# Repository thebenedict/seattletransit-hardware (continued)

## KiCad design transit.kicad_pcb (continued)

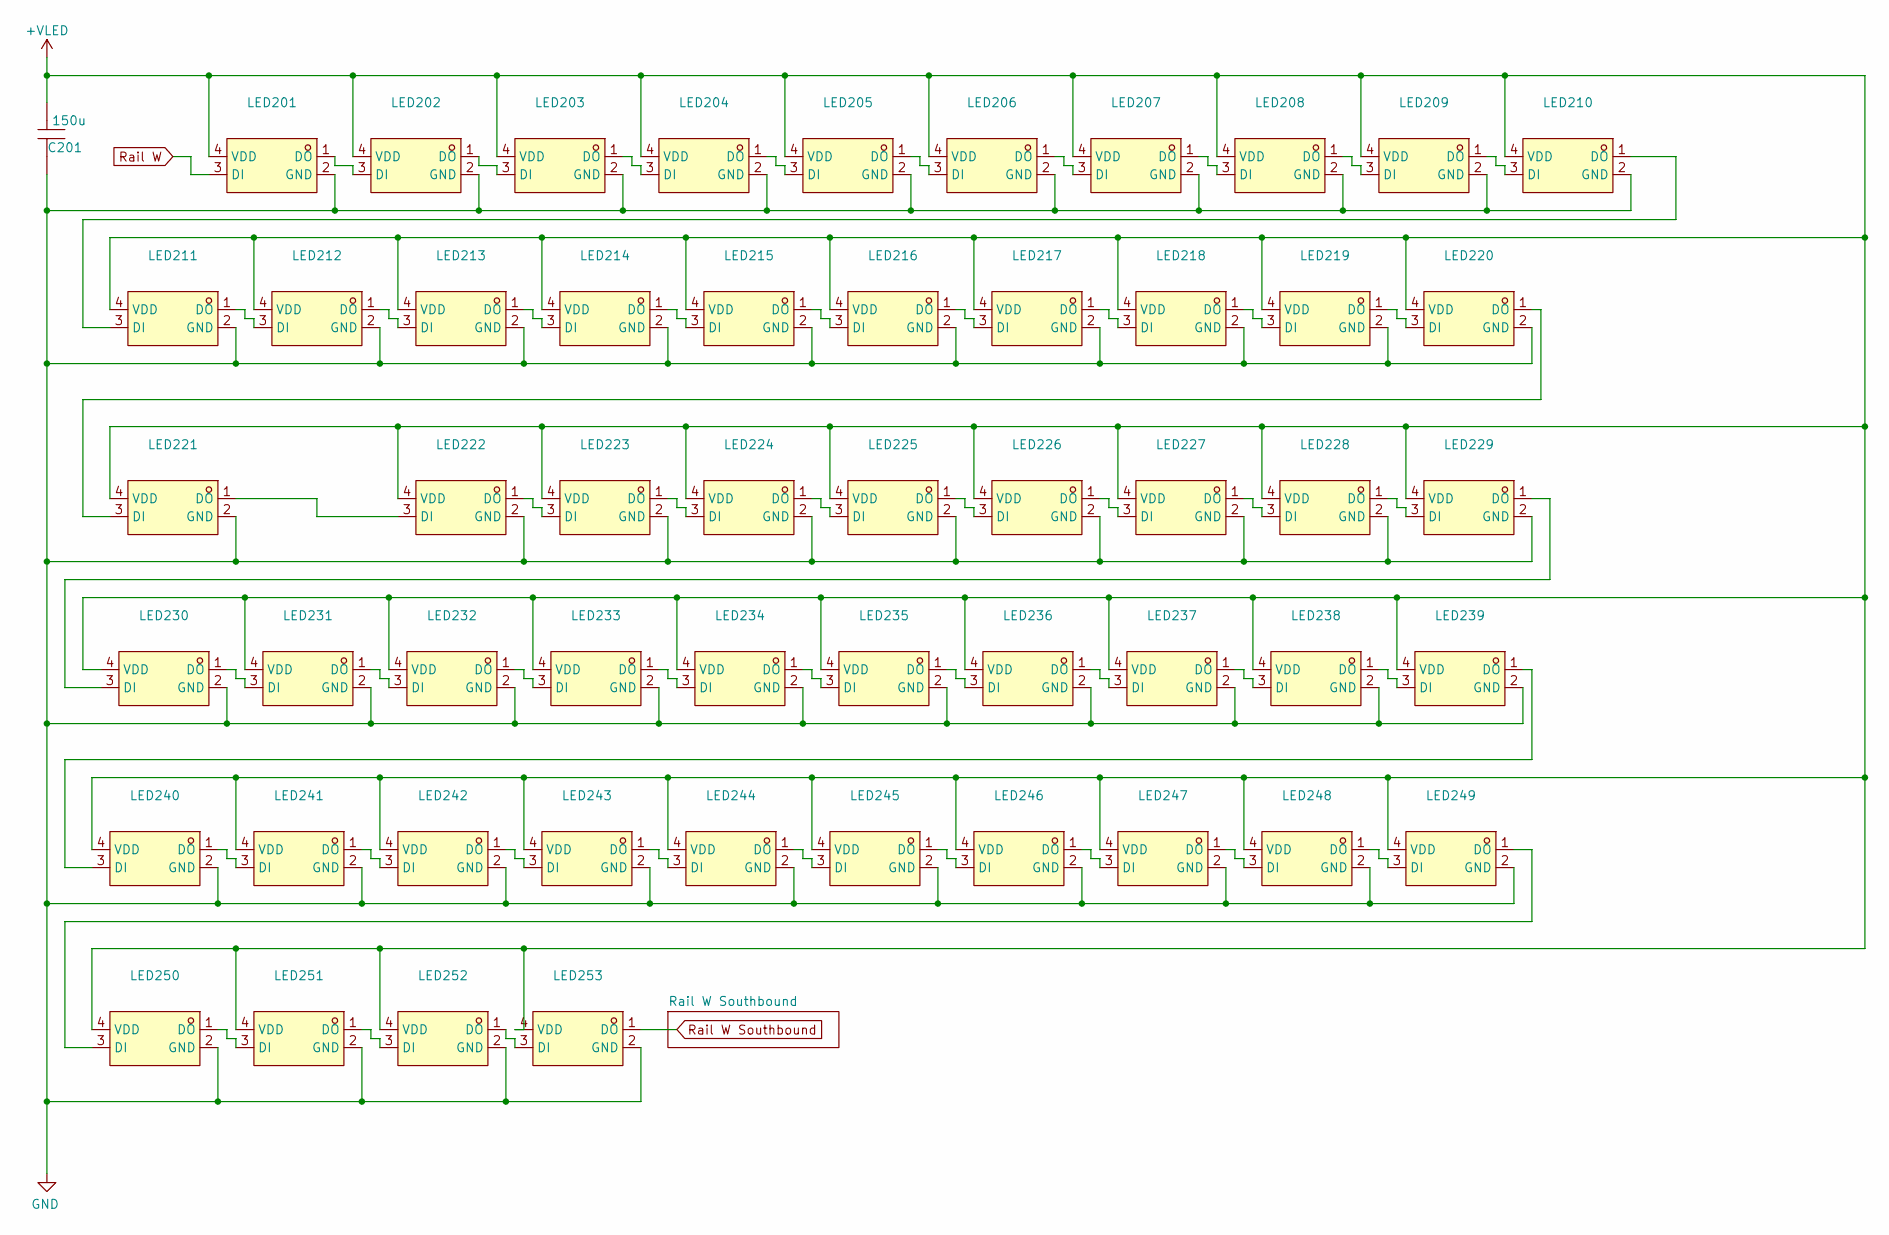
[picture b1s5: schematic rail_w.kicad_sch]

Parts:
C201: 150u; CAP-SMD_L3.5-W2.8; LCSC Part C212682
LED201, LED202, LED203, LED204, LED205, LED206, LED207, LED208, LED209, LED210, LED211, LED212, LED213, LED214, LED215, LED216, LED217, LED218, LED219, LED220, LED221, LED222, LED223, LED224, LED225, LED226, LED227, LED228, LED229, LED230, LED231, LED232, LED233, LED234, LED235, LED236, LED237, LED238, LED239, LED240, LED241, LED242, LED243, LED244, LED245, LED246, LED247, LED248, LED249, LED250, LED251, LED252, LED253: WS2812B-2020; LED-SMD_4P-L2.0-W2.0-TL_WS2812B-2020; LCSC Part C965555

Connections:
+VLED: C201.1, LED201.4 (VDD), LED202.4 (VDD), LED203.4 (VDD), LED204.4 (VDD), LED205.4 (VDD), LED206.4 (VDD), LED207.4 (VDD), LED208.4 (VDD), LED209.4 (VDD), LED210.4 (VDD), LED211.4 (VDD), LED212.4 (VDD), LED213.4 (VDD), LED214.4 (VDD), LED215.4 (VDD), LED216.4 (VDD), LED217.4 (VDD), LED218.4 (VDD), LED219.4 (VDD), LED220.4 (VDD), LED221.4 (VDD), LED222.4 (VDD), LED223.4 (VDD), LED224.4 (VDD), LED225.4 (VDD), LED226.4 (VDD), LED227.4 (VDD), LED228.4 (VDD), LED229.4 (VDD), LED230.4 (VDD), LED231.4 (VDD), LED232.4 (VDD), LED233.4 (VDD), LED234.4 (VDD), LED235.4 (VDD), LED236.4 (VDD), LED237.4 (VDD), LED238.4 (VDD), LED239.4 (VDD), LED240.4 (VDD), LED241.4 (VDD), LED242.4 (VDD), LED243.4 (VDD), LED244.4 (VDD), LED245.4 (VDD), LED246.4 (VDD), LED247.4 (VDD), LED248.4 (VDD), LED249.4 (VDD), LED250.4 (VDD), LED251.4 (VDD), LED252.4 (VDD), LED253.4 (VDD); also elsewhere on the board
GND: C201.2, LED201.2 (GND), LED202.2 (GND), LED203.2 (GND), LED204.2 (GND), LED205.2 (GND), LED206.2 (GND), LED207.2 (GND), LED208.2 (GND), LED209.2 (GND), LED210.2 (GND), LED211.2 (GND), LED212.2 (GND), LED213.2 (GND), LED214.2 (GND), LED215.2 (GND), LED216.2 (GND), LED217.2 (GND), LED218.2 (GND), LED219.2 (GND), LED220.2 (GND), LED221.2 (GND), LED222.2 (GND), LED223.2 (GND), LED224.2 (GND), LED225.2 (GND), LED226.2 (GND), LED227.2 (GND), LED228.2 (GND), LED229.2 (GND), LED230.2 (GND), LED231.2 (GND), LED232.2 (GND), LED233.2 (GND), LED234.2 (GND), LED235.2 (GND), LED236.2 (GND), LED237.2 (GND), LED238.2 (GND), LED239.2 (GND), LED240.2 (GND), LED241.2 (GND), LED242.2 (GND), LED243.2 (GND), LED244.2 (GND), LED245.2 (GND), LED246.2 (GND), LED247.2 (GND), LED248.2 (GND), LED249.2 (GND), LED250.2 (GND), LED251.2 (GND), LED252.2 (GND), LED253.2 (GND); also elsewhere on the board
unnamed: LED201.1 (DO), LED202.3 (DI)
unnamed: LED202.1 (DO), LED203.3 (DI)
unnamed: LED203.1 (DO), LED204.3 (DI)
unnamed: LED204.1 (DO), LED205.3 (DI)
unnamed: LED205.1 (DO), LED206.3 (DI)
unnamed: LED206.1 (DO), LED207.3 (DI)
unnamed: LED207.1 (DO), LED208.3 (DI)
unnamed: LED208.1 (DO), LED209.3 (DI)
unnamed: LED209.1 (DO), LED210.3 (DI)
unnamed: LED210.1 (DO), LED211.3 (DI)
unnamed: LED211.1 (DO), LED212.3 (DI)
unnamed: LED212.1 (DO), LED213.3 (DI)
unnamed: LED213.1 (DO), LED214.3 (DI)
unnamed: LED214.1 (DO), LED215.3 (DI)
unnamed: LED215.1 (DO), LED216.3 (DI)
unnamed: LED216.1 (DO), LED217.3 (DI)
unnamed: LED217.1 (DO), LED218.3 (DI)
unnamed: LED218.1 (DO), LED219.3 (DI)
unnamed: LED219.1 (DO), LED220.3 (DI)
unnamed: LED220.1 (DO), LED221.3 (DI)
unnamed: LED221.1 (DO), LED222.3 (DI)
unnamed: LED222.1 (DO), LED223.3 (DI)
unnamed: LED223.1 (DO), LED224.3 (DI)
unnamed: LED224.1 (DO), LED225.3 (DI)
unnamed: LED225.1 (DO), LED226.3 (DI)
unnamed: LED226.1 (DO), LED227.3 (DI)
unnamed: LED227.1 (DO), LED228.3 (DI)
unnamed: LED228.1 (DO), LED229.3 (DI)
unnamed: LED229.1 (DO), LED230.3 (DI)
unnamed: LED230.1 (DO), LED231.3 (DI)
unnamed: LED231.1 (DO), LED232.3 (DI)
unnamed: LED232.1 (DO), LED233.3 (DI)
unnamed: LED233.1 (DO), LED234.3 (DI)
unnamed: LED234.1 (DO), LED235.3 (DI)
unnamed: LED235.1 (DO), LED236.3 (DI)
unnamed: LED236.1 (DO), LED237.3 (DI)
unnamed: LED237.1 (DO), LED238.3 (DI)
unnamed: LED238.1 (DO), LED239.3 (DI)
unnamed: LED239.1 (DO), LED240.3 (DI)
unnamed: LED240.1 (DO), LED241.3 (DI)
unnamed: LED241.1 (DO), LED242.3 (DI)
unnamed: LED242.1 (DO), LED243.3 (DI)
unnamed: LED243.1 (DO), LED244.3 (DI)
unnamed: LED244.1 (DO), LED245.3 (DI)
unnamed: LED245.1 (DO), LED246.3 (DI)
unnamed: LED246.1 (DO), LED247.3 (DI)
unnamed: LED247.1 (DO), LED248.3 (DI)
unnamed: LED248.1 (DO), LED249.3 (DI)
unnamed: LED249.1 (DO), LED250.3 (DI)
unnamed: LED250.1 (DO), LED251.3 (DI)
unnamed: LED251.1 (DO), LED252.3 (DI)
unnamed: LED252.1 (DO), LED253.3 (DI)
Rail W: LED201.3 (DI); also elsewhere on the board
Rail W Southbound: LED253.1 (DO); also elsewhere on the board

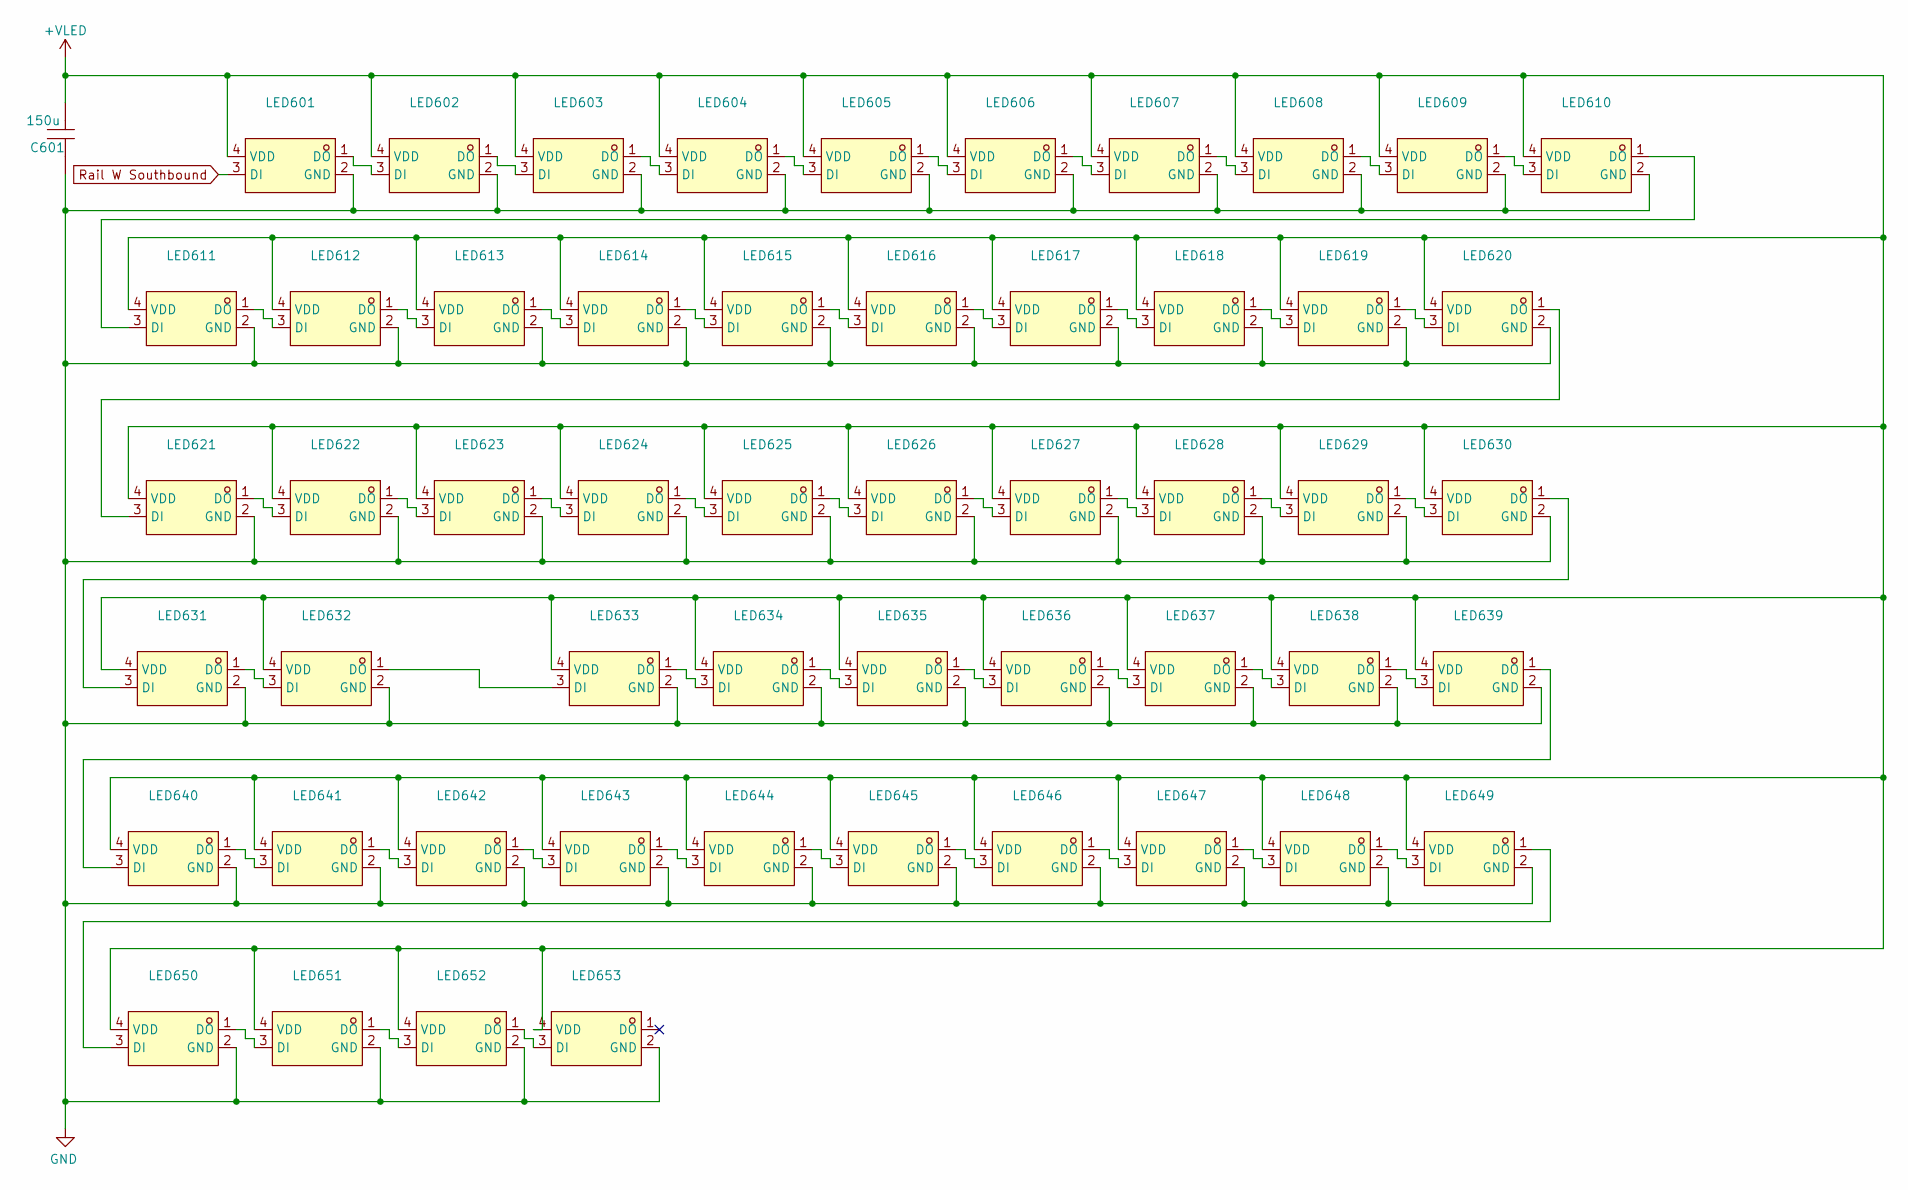
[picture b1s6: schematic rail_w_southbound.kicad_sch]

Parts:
C601: 150u; CAP-SMD_L3.5-W2.8; LCSC Part C212682
LED601, LED602, LED603, LED604, LED605, LED606, LED607, LED608, LED609, LED610, LED611, LED612, LED613, LED614, LED615, LED616, LED617, LED618, LED619, LED620, LED621, LED622, LED623, LED624, LED625, LED626, LED627, LED628, LED629, LED630, LED631, LED632, LED633, LED634, LED635, LED636, LED637, LED638, LED639, LED640, LED641, LED642, LED643, LED644, LED645, LED646, LED647, LED648, LED649, LED650, LED651, LED652, LED653: WS2812B-2020; LED-SMD_4P-L2.0-W2.0-TL_WS2812B-2020; LCSC Part C965555

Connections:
+VLED: C601.1, LED601.4 (VDD), LED602.4 (VDD), LED603.4 (VDD), LED604.4 (VDD), LED605.4 (VDD), LED606.4 (VDD), LED607.4 (VDD), LED608.4 (VDD), LED609.4 (VDD), LED610.4 (VDD), LED611.4 (VDD), LED612.4 (VDD), LED613.4 (VDD), LED614.4 (VDD), LED615.4 (VDD), LED616.4 (VDD), LED617.4 (VDD), LED618.4 (VDD), LED619.4 (VDD), LED620.4 (VDD), LED621.4 (VDD), LED622.4 (VDD), LED623.4 (VDD), LED624.4 (VDD), LED625.4 (VDD), LED626.4 (VDD), LED627.4 (VDD), LED628.4 (VDD), LED629.4 (VDD), LED630.4 (VDD), LED631.4 (VDD), LED632.4 (VDD), LED633.4 (VDD), LED634.4 (VDD), LED635.4 (VDD), LED636.4 (VDD), LED637.4 (VDD), LED638.4 (VDD), LED639.4 (VDD), LED640.4 (VDD), LED641.4 (VDD), LED642.4 (VDD), LED643.4 (VDD), LED644.4 (VDD), LED645.4 (VDD), LED646.4 (VDD), LED647.4 (VDD), LED648.4 (VDD), LED649.4 (VDD), LED650.4 (VDD), LED651.4 (VDD), LED652.4 (VDD), LED653.4 (VDD); also elsewhere on the board
GND: C601.2, LED601.2 (GND), LED602.2 (GND), LED603.2 (GND), LED604.2 (GND), LED605.2 (GND), LED606.2 (GND), LED607.2 (GND), LED608.2 (GND), LED609.2 (GND), LED610.2 (GND), LED611.2 (GND), LED612.2 (GND), LED613.2 (GND), LED614.2 (GND), LED615.2 (GND), LED616.2 (GND), LED617.2 (GND), LED618.2 (GND), LED619.2 (GND), LED620.2 (GND), LED621.2 (GND), LED622.2 (GND), LED623.2 (GND), LED624.2 (GND), LED625.2 (GND), LED626.2 (GND), LED627.2 (GND), LED628.2 (GND), LED629.2 (GND), LED630.2 (GND), LED631.2 (GND), LED632.2 (GND), LED633.2 (GND), LED634.2 (GND), LED635.2 (GND), LED636.2 (GND), LED637.2 (GND), LED638.2 (GND), LED639.2 (GND), LED640.2 (GND), LED641.2 (GND), LED642.2 (GND), LED643.2 (GND), LED644.2 (GND), LED645.2 (GND), LED646.2 (GND), LED647.2 (GND), LED648.2 (GND), LED649.2 (GND), LED650.2 (GND), LED651.2 (GND), LED652.2 (GND), LED653.2 (GND); also elsewhere on the board
unnamed: LED601.1 (DO), LED602.3 (DI)
unnamed: LED602.1 (DO), LED603.3 (DI)
unnamed: LED603.1 (DO), LED604.3 (DI)
unnamed: LED604.1 (DO), LED605.3 (DI)
unnamed: LED605.1 (DO), LED606.3 (DI)
unnamed: LED606.1 (DO), LED607.3 (DI)
unnamed: LED607.1 (DO), LED608.3 (DI)
unnamed: LED608.1 (DO), LED609.3 (DI)
unnamed: LED609.1 (DO), LED610.3 (DI)
unnamed: LED610.1 (DO), LED611.3 (DI)
unnamed: LED611.1 (DO), LED612.3 (DI)
unnamed: LED612.1 (DO), LED613.3 (DI)
unnamed: LED613.1 (DO), LED614.3 (DI)
unnamed: LED614.1 (DO), LED615.3 (DI)
unnamed: LED615.1 (DO), LED616.3 (DI)
unnamed: LED616.1 (DO), LED617.3 (DI)
unnamed: LED617.1 (DO), LED618.3 (DI)
unnamed: LED618.1 (DO), LED619.3 (DI)
unnamed: LED619.1 (DO), LED620.3 (DI)
unnamed: LED620.1 (DO), LED621.3 (DI)
unnamed: LED621.1 (DO), LED622.3 (DI)
unnamed: LED622.1 (DO), LED623.3 (DI)
unnamed: LED623.1 (DO), LED624.3 (DI)
unnamed: LED624.1 (DO), LED625.3 (DI)
unnamed: LED625.1 (DO), LED626.3 (DI)
unnamed: LED626.1 (DO), LED627.3 (DI)
unnamed: LED627.1 (DO), LED628.3 (DI)
unnamed: LED628.1 (DO), LED629.3 (DI)
unnamed: LED629.1 (DO), LED630.3 (DI)
unnamed: LED630.1 (DO), LED631.3 (DI)
unnamed: LED631.1 (DO), LED632.3 (DI)
unnamed: LED632.1 (DO), LED633.3 (DI)
unnamed: LED633.1 (DO), LED634.3 (DI)
unnamed: LED634.1 (DO), LED635.3 (DI)
unnamed: LED635.1 (DO), LED636.3 (DI)
unnamed: LED636.1 (DO), LED637.3 (DI)
unnamed: LED637.1 (DO), LED638.3 (DI)
unnamed: LED638.1 (DO), LED639.3 (DI)
unnamed: LED639.1 (DO), LED640.3 (DI)
unnamed: LED640.1 (DO), LED641.3 (DI)
unnamed: LED641.1 (DO), LED642.3 (DI)
unnamed: LED642.1 (DO), LED643.3 (DI)
unnamed: LED643.1 (DO), LED644.3 (DI)
unnamed: LED644.1 (DO), LED645.3 (DI)
unnamed: LED645.1 (DO), LED646.3 (DI)
unnamed: LED646.1 (DO), LED647.3 (DI)
unnamed: LED647.1 (DO), LED648.3 (DI)
unnamed: LED648.1 (DO), LED649.3 (DI)
unnamed: LED649.1 (DO), LED650.3 (DI)
unnamed: LED650.1 (DO), LED651.3 (DI)
unnamed: LED651.1 (DO), LED652.3 (DI)
unnamed: LED652.1 (DO), LED653.3 (DI)
Rail W Southbound: LED601.3 (DI); also elsewhere on the board

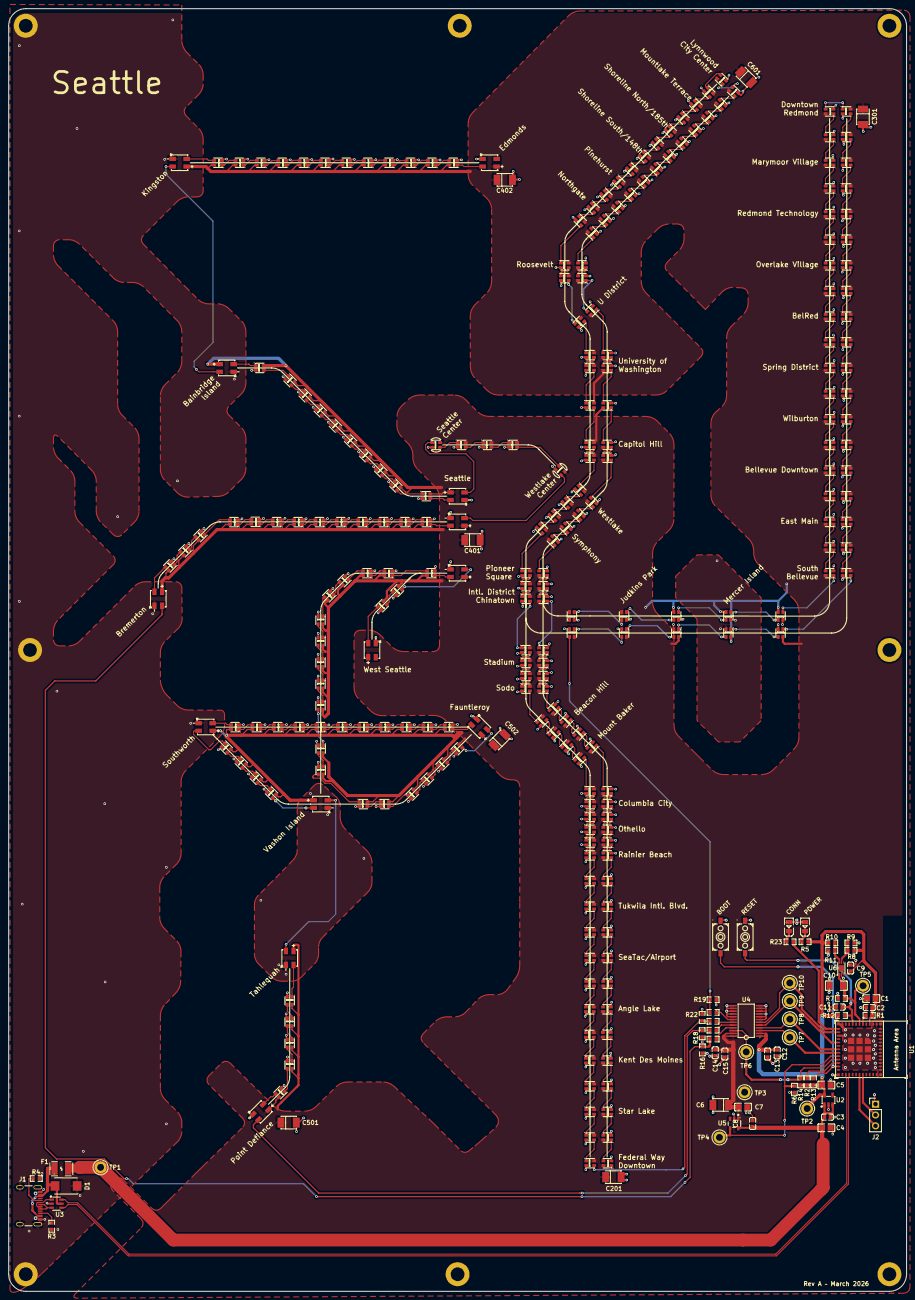
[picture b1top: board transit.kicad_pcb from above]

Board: 2 copper layers, 210.0 x 300.0 mm, 324 parts (0 on the bottom side), 280 nets.

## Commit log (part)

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2026-03-13 hello world
2026-03-16 PCBA prototype order
2026-04-10 Add images, stub README
2026-05-20 Rev B component layout
2026-05-21 Add basemap, rerouting checkpoint
2026-05-23 Sounder and T silk, before scripting
2026-05-23 scripting, checkpoint
2026-05-23 layout water taxi
2026-05-24 sounder layout checkpoint
2026-05-24 initial layout checkpoint
2026-05-26 pier 50 routing checkpoint
2026-05-27 checkpoint before stopping double routing
2026-05-27 single ferry track checkpoint
2026-05-28 checkpoint before label plugin
2026-05-28 Initial LED placement complete
2026-05-29 Add rail labels
2026-05-29 station labels
2026-05-29 more room for sounder_s and monorail, label fixes
2026-06-02 checkpoint
2026-06-23 cleanup
2026-06-25 Route main circuit
2026-06-25 route T
2026-06-25 Renumber Sounder, ready to route
2026-06-26 route sounder
2026-06-26 route link 1
2026-06-26 route link 2
2026-06-26 route monorail
2026-06-26 Rail routed, add rectangle to Seattle port
2026-06-26 Route point defiance tahlequah
2026-06-28 junction checkpoint
2026-06-28 routing complete
2026-06-28 reflow reference designators
2026-06-28 refresh decoration yaml
2026-06-30 rev-b validation run
